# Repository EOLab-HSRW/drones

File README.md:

# EOLab's Drones System

EOLab's Drone System aims to provide a framework that serves as an umbrella to operate all our self-built drones. In this documentation you will find all the necessary resources for: specifications of our drones, 3D models for reference, operation manuals and general conventions used in all our platforms.

> [!IMPORTANT]
> If you are new, the best way to start is reading the ➡️ [Introduction](/introduction/) ⬅️ for these docs.

> The [EOLab](https://www.eolab.de/) (Earth Observation Lab) is a laboratory of the [Rhine-Waal University of Applied Sciences (HSRW)](https://www.hochschule-rhein-waal.de/de) in Germany. It is part of the [Faculty of Communication and Environment](https://www.hochschule-rhein-waal.de/de/fakultaeten/kommunikation-und-umwelt), Campus Kamp-Lintfort.

## Drones

| Drone Name                                                                                                                                       | Self-built | Quantity | Status               |
|--------------------------------------------------------------------------------------------------------------------------------------------------|:----------:|:--------:|----------------------|
| [SAR](./sar/)                                                                                                                                    | ✅         | 1        | 🟡 Under test        |
| [Platypus](./platypus/)                                                                                                                          | ✅         | 1        | 🟡 Under test        |
| [Protoflyer](./protoflyer/)                                                                                                                      | ✅         | ?        | 🟡 Under test        |
| [Phoenix](./phoenix/)                                                                                                                            | ✅         | 1        | 🟡 Under test        |
| [Condor](./condor/)                                                                                                                              | ✅         | 1        | 🟡 Under test        |
| [Pegasus](./pegasus/)                                                                                                                            | ✅         | 1        | 🟡 Under test        |
| Octopus                                                                                                                                          | ✅         | 1        | 🟡 Under maintenance |
| Mantis                                                                                                                                           | ✅         | 1        | 🟡 Under maintenance |
| Cargo Drone                                                                                                                                      | ✅         | 1        | 🟡 Under maintenance |
| DJI Tello EDU <br> - [User Manual](https://dl-cdn.ryzerobotics.com/downloads/Tello/Tello%20User%20Manual%20v1.4.pdf)                             |            | 2?       | 🟢 Operational       |
| DJI RoboMaster TT Tello Talent <br> - [User Manual](https://dl.djicdn.com/downloads/RoboMaster+TT/RoboMaster_TT_Tello_Talent_User_Manual_en.pdf) |            | ?        | 🟢 Operational       |
| DJI Phantom 4 Pro <br> - [User Manual](https://dl.djicdn.com/downloads/phantom_4_pro/Phantom+4+Pro+Pro+Plus+User+Manual+v1.0.pdf)                |            | 1        | 🟢 Operational       |
| DJI NEO <br> - [User Manual](https://dl.djicdn.com/downloads/neo/20240905/DJI_Neo_User_Manual_v1.0_en.pdf)                                       |            | 1        | 🟢 Operational       |
| DJI Mini 4 Pro <br> - [User Manual](https://dl.djicdn.com/downloads/DJI_Mini_4_Pro/DJI_Mini_4_Pro_User_Manual_EN.pdf)                            |            | 1        | 🟢 Operational       |
| DJI Avata <br> - [User Manual](https://www.foto.no/media/multicase/documents/dji/dji%20avata%20user%20manual%20v1.06.pdf)                        |            | 1        | 🟢 Operational       |
| DJI Mavic 3M <br> - [User Manual](https://dl.djicdn.com/downloads/DJI_Mavic_3_Enterprise/20221216/DJI_Mavic_3M_User_Manual-EN.pdf)               |            | 1        | 🟢 Operational       |
| AR Drone 2.0                                                                                                                                     |            | 2        | 🟢 Operational       |

## Components

In our system, a "component" can be any extra device like a RC Controller or a payload that interact with the our drones. Our system components are designed to be combinable, so that they can be interchanged with any of our self-built drones, all the necessary parameters to integrate the component(s) into the drone are added in the drone firmware.

| Component                                                                                                                                                                                                                           | Quantity | Compatibility      |
|-------------------------------------------------------------------------------------------------------------------------------------------------------------------------------------------------------------------------------------|:--------:|--------------------|
| [Radiomaster TX16s (with ELRS radio module)](https://www.radiomasterrc.com/products/tx16s-mark-ii-radio-controller?variant=45864311685351)<br> - [User Manual](https://cdn.shopify.com/s/files/1/0609/8324/7079/files/TX16S_1.pdf)  | 1        | only `self-builts` |
| [RP1 V2 Receiver (with external antenna)](https://www.radiomasterrc.com/products/rp1-expresslrs-2-4ghz-nano-receiver) <br> - [User Manual](https://cdn.shopify.com/s/files/1/0609/8324/7079/files/RP1_User_Manual.pdf?v=1722923320) | 2?       | only `self-builts`  |
| [RP2 V2 Receiver (with ceramic antenna)](https://www.radiomasterrc.com/products/rp2-expresslrs-2-4ghz-nano-receiver) <br> - [User Manual](https://cdn.shopify.com/s/files/1/0609/8324/7079/files/RP2_User_Manual.pdf?v=1722923303)  | 2?       | only `self-builts`  |
| [EMLID Reach RS3](https://emlid.com/reachrs3/)<br> - [User Manual](https://docs.emlid.com/reachrs3/) | 2 | for DJI drones |
| [EMLID Reach RS2+](https://emlid.com/reachrs2plus/)<br> - [User Manual](https://docs.emlid.com/reachrs2/) | 2 | for DJI drones |

## Misc Utils

| Type    | Misc Utils                                                                                                                                                                                                                                                                                                                                                                                                                          | Quantity |
|---------|-------------------------------------------------------------------------------------------------------------------------------------------------------------------------------------------------------------------------------------------------------------------------------------------------------------------------------------------------------------------------------------------------------------------------------------|----------|
| Charger | Graupner Ultramat 18 (Graupner went bankrupt in 2012)<br> - [User Manual](https://www.manualslib.de/manual/51049/Graupner-Ultramat-18.html)                                                                                                                                                                                                                                                                                         | 1        |
| Charger | [Voltcraft V-Charge 200 DUO](https://www.conrad.de/de/p/voltcraft-v-charge-200-duo-modellbau-multifunktionsladegeraet-12-v-230-v-10-a-blei-nimh-nicd-lipo-liion-lihv-blei-1539603.html)<br> - [User Manual](https://asset.conrad.com/media10/add/160267/c1/-/en/001539603ML02/upute-za-rukovanje-1539603-voltcraft-v-charge-200-duo-visenamjenski-punjac-baterija-za-modele-12-v-230-v-10-a-olovni-nikalj-metal-hidridni-nikal.pdf) | 1        |
| Charger | iMax B6AC <br> - [User Manual](https://www.pololu.com/file/0j525/imaxb6acmanual.pdf)                                                                                                                                                                                                                                                                                                                                                | 1        |
| Charger | [Tattu TA3000 Dual Smart Charger](https://genstattu.com/tattu-dual-smart-charger-60a-3000w-for-6s-12s-14s-lipo-lihv-tattu-smart-battery/)<br> - [User Manual](https://genstattu.com/content/instock/TA3000.pdf?srsltid=AfmBOoqkx91cG-YnTiC2ZcBJFpmeLNBOX0O4IQl7vUg3wHW8a9Hnu5sL)                                                                                                                                                    | 1        |

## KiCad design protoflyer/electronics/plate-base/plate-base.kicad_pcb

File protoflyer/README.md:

# Protoflyer

## Components

| Component | Model                                     | Ref Link                                                             | Documentation                                                                                         |
|-----------|-------------------------------------------|----------------------------------------------------------------------|-------------------------------------------------------------------------------------------------------|
| FMU       | Hex Cube Black                            | [link](https://docs.px4.io/main/en/flight_controller/pixhawk-2.html) | [The Cube Module Overview](https://docs.cubepilot.org/user-guides/autopilot/the-cube-module-overview) |
| Motor     | DJI 2312E Motor (as part of the DJI E305) | (obsolete)                                                           | [DJI E305 Propulsion System](https://dl.djicdn.com/downloads/e305/en/E305_User_Manual_v1.00_en.pdf)   |
| ESC       | DJI 420LITE ESC (as part of the DJI E305) | (obsolete)                                                           | [DJI E305 Propulsion System](https://dl.djicdn.com/downloads/e305/en/E305_User_Manual_v1.00_en.pdf)   |
| Propeller | DJI 9450 (as part of the DJI E305)        | (obsolete)                                                           | [DJI E305 Propulsion System](https://dl.djicdn.com/downloads/e305/en/E305_User_Manual_v1.00_en.pdf)   |

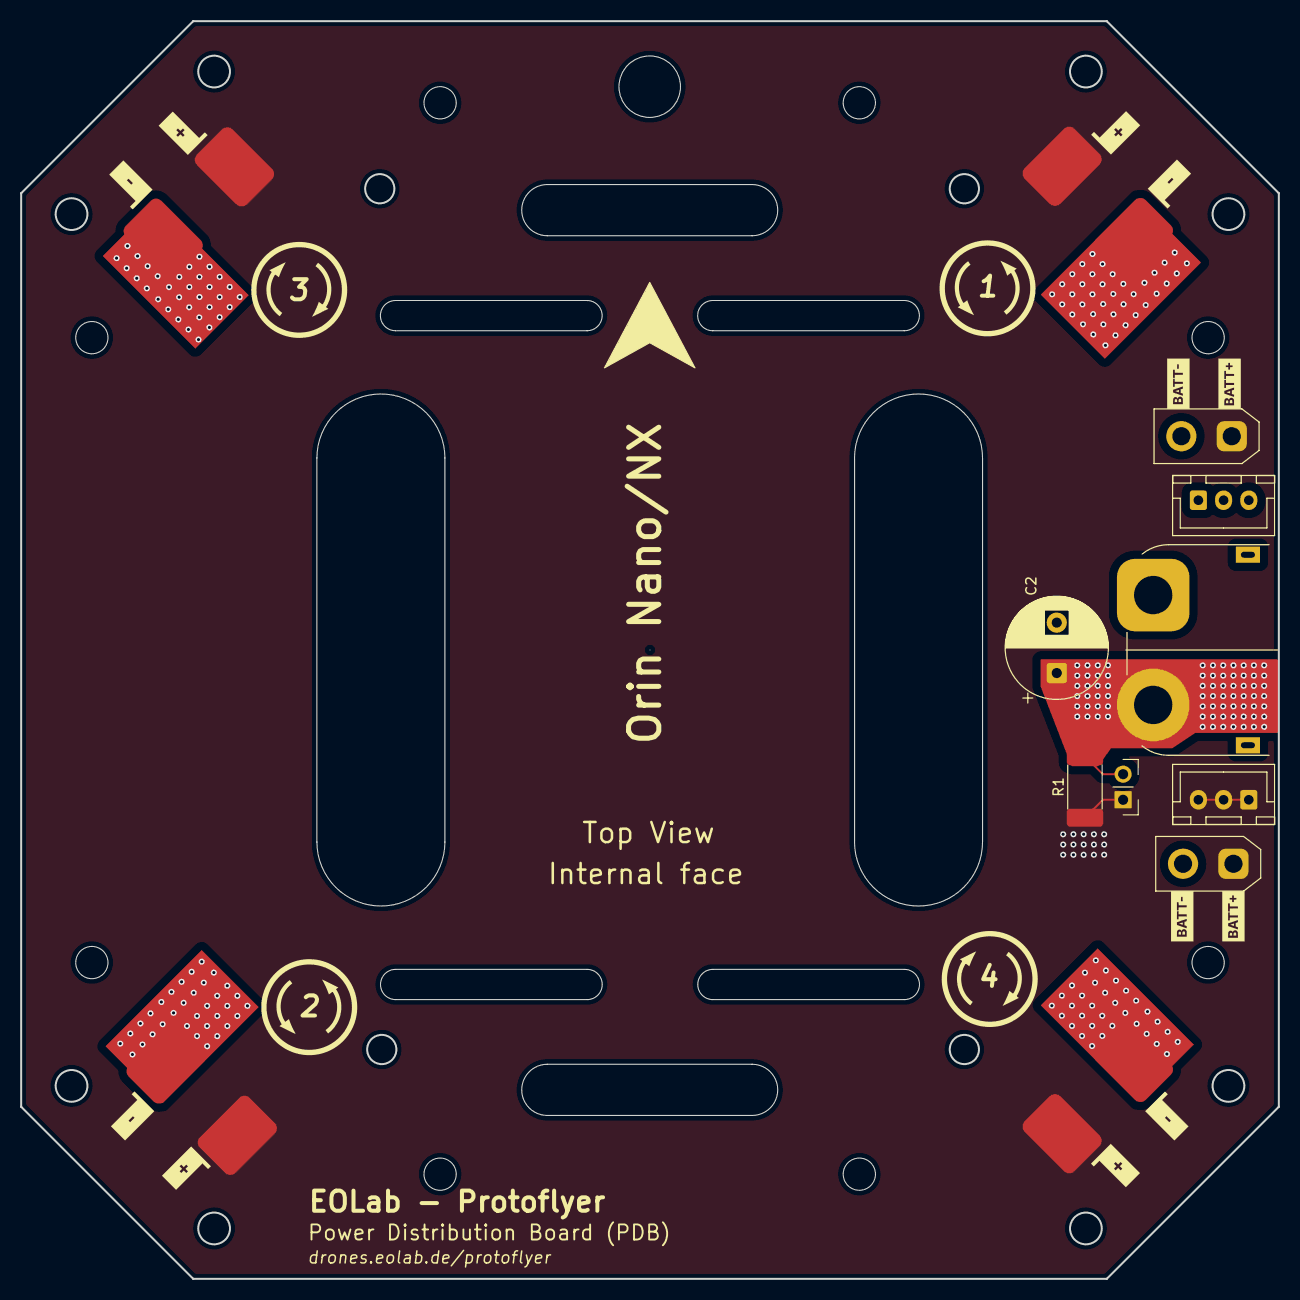
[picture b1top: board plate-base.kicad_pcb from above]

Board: 2 copper layers, 124.8 x 124.8 mm, 12 parts (0 on the bottom side), 3 nets.

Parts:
C2: 470u, 50V, 20%; CP_Radial_D10.0mm_P5.00mm
J1: Conn_01x02_Socket; AMASS_XT90PW-M_1x02_P10.90mm_Horizontal
J2, J3, J4, J5: Conn_01x02_Pin; Motor Solder Pad
J6, J11: Conn_01x03_Pin; JST_XH_B3B-XH-A_1x03_P2.50mm_Vertical
J8, J9: Conn_01x02_Pin; AMASS_XT30UPB-F_1x02_P5.0mm_Vertical
J10: Conn_01x02_Pin; PinHeader_1x02_P2.54mm_Vertical
R1: 500u, 1%, 10 W; R_2512_6332Metric_Pad1.40x3.35mm_HandSolder

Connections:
+BATT: C2.1, J1.2, J10.2, R1.4
-BATT: C2.2, J1.1, J2.2, J3.2, J4.2, J5.2, J6.1, J6.2, J6.3, J8.2, J9.2
VBUS: J2.1, J3.1, J4.1, J5.1, J8.1, J9.1, J10.1, J11.1, J11.2, J11.3, R1.1

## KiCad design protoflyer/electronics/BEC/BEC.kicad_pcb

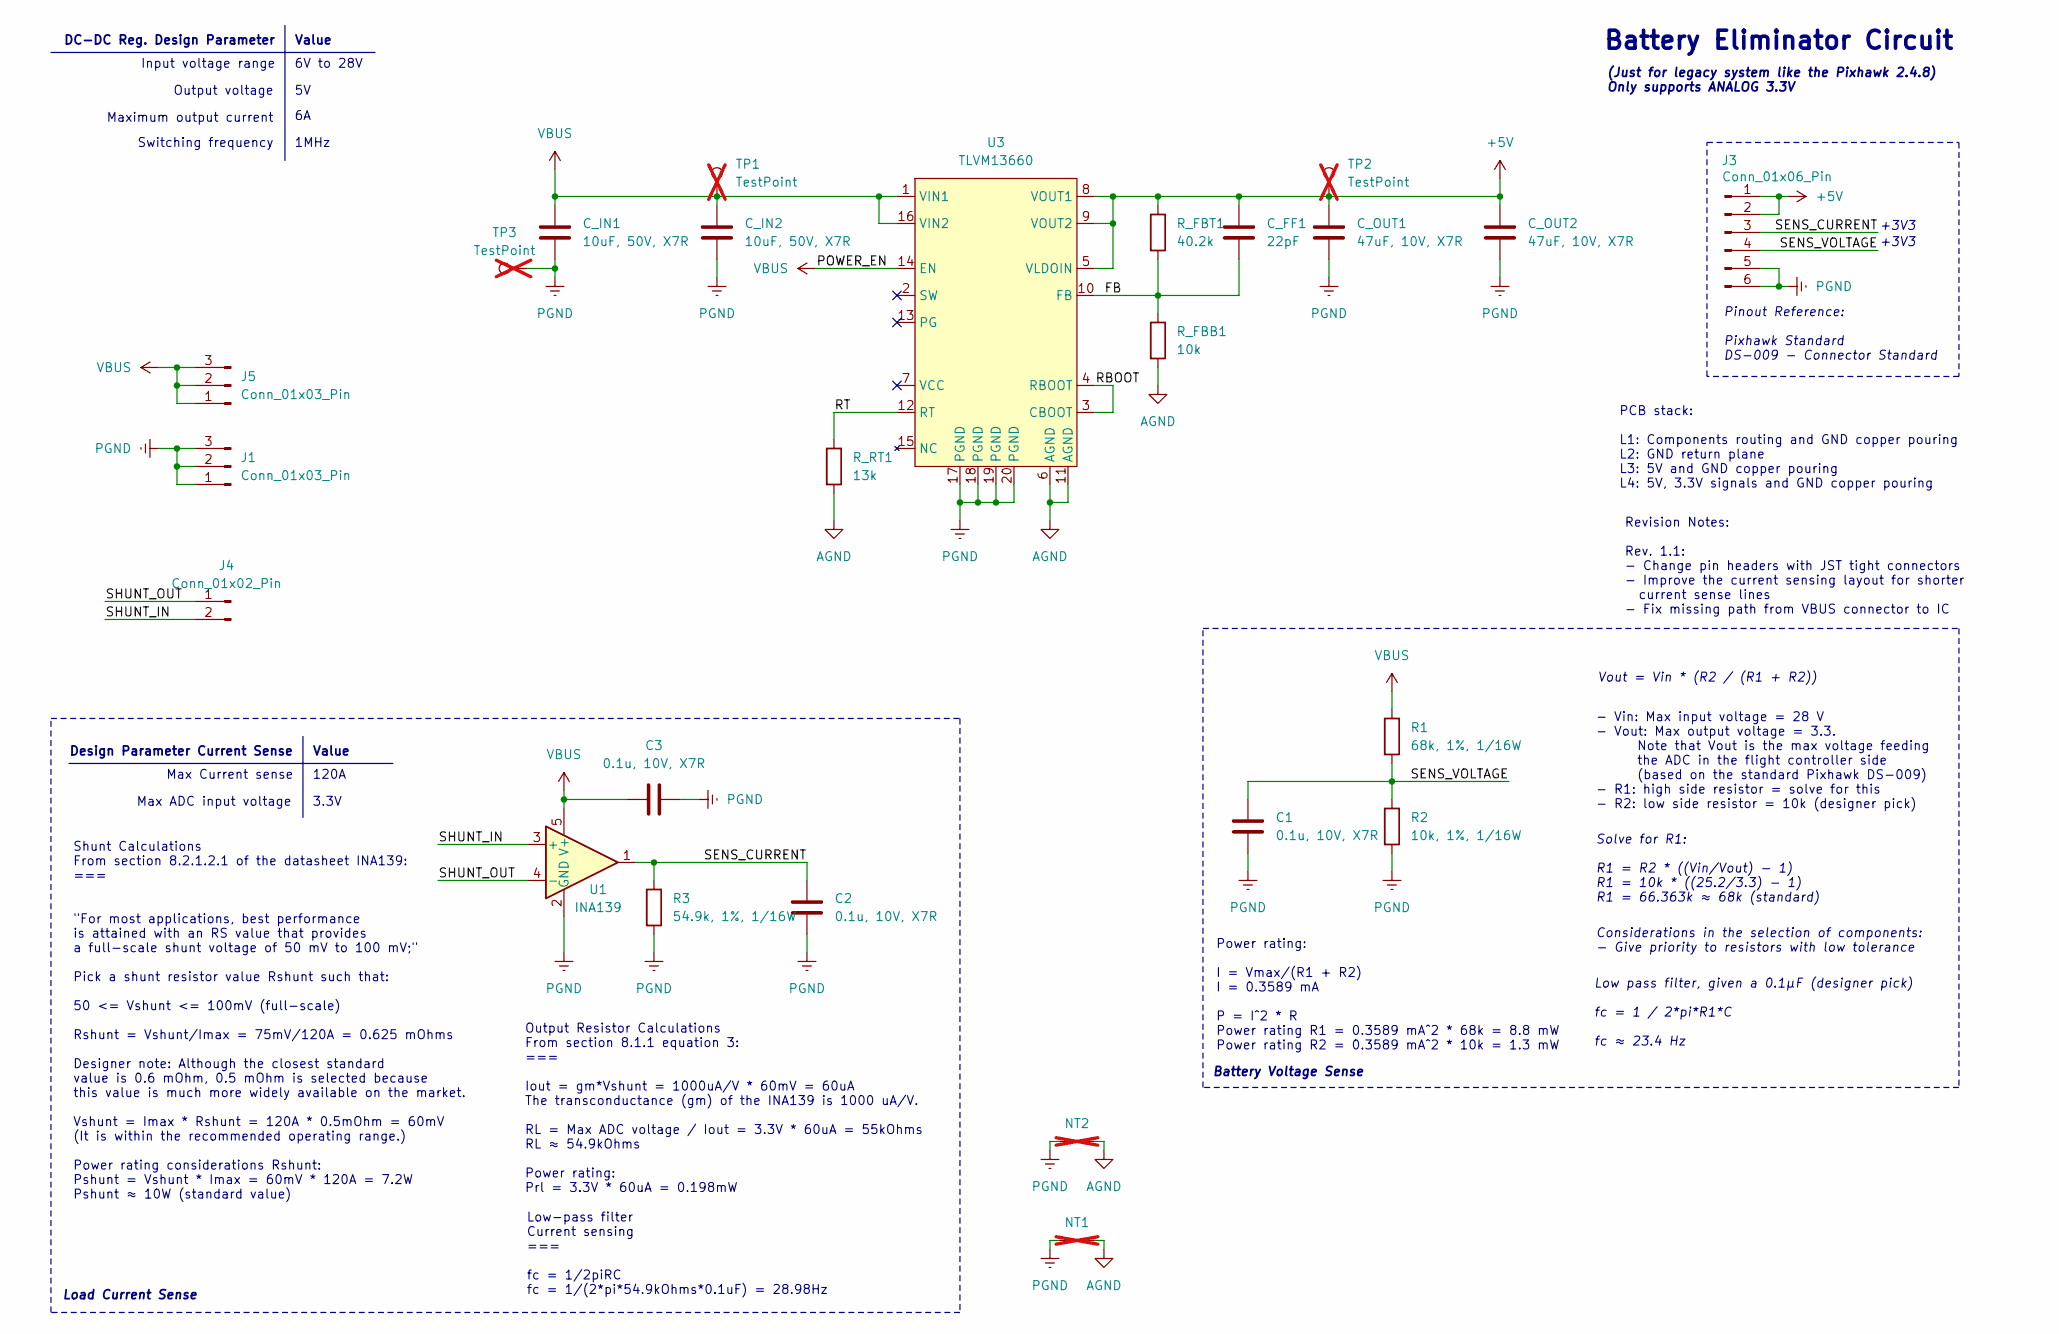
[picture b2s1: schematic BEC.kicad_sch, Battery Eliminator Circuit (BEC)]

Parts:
C1, C2, C3: 0.1u, 10V, X7R; C_0402_1005Metric_Pad0.74x0.62mm_HandSolder; Digikey No 587-3769-1-ND
C_FF1: 22pF; C_0402_1005Metric_Pad0.74x0.62mm_HandSolder; Digikey No 732-7427-1-ND
C_IN1, C_IN2: 10uF, 50V, X7R; C_1210_3225Metric_Pad1.33x2.70mm_HandSolder; Digikey No 587-3166-1-ND
C_OUT1, C_OUT2: 47uF, 10V, X7R; C_1210_3225Metric_Pad1.33x2.70mm_HandSolder; Digikey No 587-5921-1-ND
J1, J5: Conn_01x03_Pin; SHDR3W80P0X250_1X3_1000X600X950P; Digikey No 455-2966-ND
J3: Conn_01x06_Pin; JST_GH_SM06B-GHS-TB_1x06-1MP_P1.25mm_Horizontal; Digikey No 455-1568-2-ND
J4: Conn_01x02_Pin; PinHeader_1x02_P2.54mm_Vertical
NT1, NT2: NetTie_2; NetTie-2_SMD_Pad0.5mm; not fitted
R1: 68k, 1%, 1/16W; R_0402_1005Metric; Digikey No RMCF0402FT68K0CT-ND
R2: 10k, 1%, 1/16W; R_0402_1005Metric; Digikey No RMCF0402FT10K0CT-ND
R3: 54.9k, 1%, 1/16W; R_0402_1005Metric; Digikey No 13-RC0402FR-1354K9LCT-ND
R_FBB1: 10k; R_0603_1608Metric_Pad0.98x0.95mm_HandSolder; Digikey No 311-10.0KHRCT-ND
R_FBT1: 40.2k; R_0603_1608Metric_Pad0.98x0.95mm_HandSolder; Digikey No 311-40.2KHRCT-ND
R_RT1: 13k; R_0603_1608Metric_Pad0.98x0.95mm_HandSolder; Digikey No 311-13.0KHRCT-ND
TP1, TP2, TP3: TestPoint; TestPoint_Pad_D1.0mm; not fitted
U1: INA139; SOT-23-5; Digikey No INA139NA/250CT-ND
U3: TLVM13660; B3QFN20_RDL_TEX; Digikey No 296-TLVM13660RDLRCT-ND

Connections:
+5V: C_FF1.1, C_OUT1.1, C_OUT2.1, J3.1, J3.2, R_FBT1.1, TP2.1, U3.5 (VLDOIN), U3.8 (VOUT1), U3.9 (VOUT2)
/FB: C_FF1.2, R_FBB1.1, R_FBT1.2, U3.10 (FB)
/RBOOT: U3.3 (CBOOT), U3.4 (RBOOT)
/RT: R_RT1.1, U3.12 (RT)
/SENS_CURRENT: C2.1, J3.3, R3.1, U1.1
/SENS_VOLTAGE: C1.1, J3.4, R1.2, R2.1
/SHUNT_IN: J4.2, U1.3 (+)
/SHUNT_OUT: J4.1, U1.4 (-)
AGND: NT1.2, NT2.2, R_FBB1.2, R_RT1.2, U3.6 (AGND), U3.11 (AGND)
PGND: C1.2, C2.2, C3.2, C_IN1.2, C_IN2.2, C_OUT1.2, C_OUT2.2, J1.1, J1.2, J1.3, J3.5, J3.6, NT1.1, NT2.1, R2.2, R3.2, TP3.1, U1.2 (GND), U3.17 (PGND), U3.18 (PGND), U3.19 (PGND), U3.20 (PGND)
VBUS: C3.1, C_IN1.1, C_IN2.1, J5.1, J5.2, J5.3, R1.1, TP1.1, U1.5 (V+), U3.1 (VIN1), U3.14 (EN), U3.16 (VIN2)

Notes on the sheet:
Revision Notes: Rev. 1.1: - Change pin headers with JST tight connectors - Improve the current sensing layout for shorter current sense lines - Fix missing path from VBUS connector to IC
DC-DC Reg. Design Parameter
Load Current Sense
+3V3
Solve for R1: R1 = R2 * ((Vin/Vout) - 1) R1 = 10k * ((25.2/3.3) - 1) R1 = 66.363k ≈ 68k (standard)
Value
Pinout Reference: Pixhawk Standard DS-009 - Connector Standard
Maximum output current
Switching frequency
Battery Voltage Sense
PCB stack: L1: Components routing and GND copper pouring L2: GND return plane L3: 5V and GND copper pouring L4: 5V, 3.3V signals and GND copper pouring
Max Current sense
Vout = Vin * (R2 / (R1 + R2))
Design Parameter Current Sense
Shunt Calculations From section 8.2.1.2.1 of the datasheet INA139: === "For most applications, best performance is attained with an RS value that provides a full-scale shunt voltage of 50 mV to 100 mV;" Pick a shunt resistor value Rshunt such that: 50 <= Vshunt <= 100mV (full-scale) Rshunt = Vshunt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
Power rating: I = Vmax/(R1 + R2) I = 0.3589 mA P = I^2 * R Power rating R1 = 0.3589 mA^2 * 68k = 8.8 mW Power rating R2 = 0.3589 mA^2 * 10k = 1.3 mW
- Vin: Max input voltage = 28 V - Vout: Max output voltage = 3.3. Note that Vout is the max voltage feeding the ADC in the flight controller side (based on the standard Pixhawk DS-009) - R1: high side resistor = solve for this - R2: low side resistor = 10k (designer pick)
Output Resistor Calculations From section 8.1.1 equation 3: === Iout = gm*Vshunt = 1000uA/V * 60mV = 60uA The transconductance (gm) of the INA139 is 1000 uA/V. RL = Max ADC voltage / Iout = 3.3V * 60uA = 55kOhms RL ≈ 54.9kOhms Power rating: Prl = 3.3V * 60uA = 0.198mW
(Just for legacy system like the Pixhawk 2.4.8) Only supports ANALOG 3.3V
1MHz
120A
Battery Eliminator Circuit
Max ADC input voltage
Considerations in the selection of components: - Give priority to resistors with low tolerance
Low pass filter, given a 0.1μF (designer pick) fc = 1 / 2*pi*R1*C fc ≈ 23.4 Hz
Input voltage range
Low-pass filter Current sensing === fc = 1/2piRC fc = 1/(2*pi*54.9kOhms*0.1uF) = 28.98Hz
6V to 28V
Output voltage
3.3V

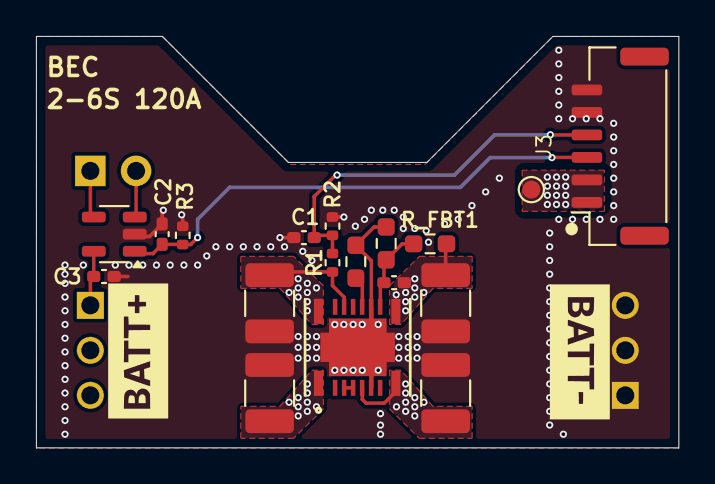
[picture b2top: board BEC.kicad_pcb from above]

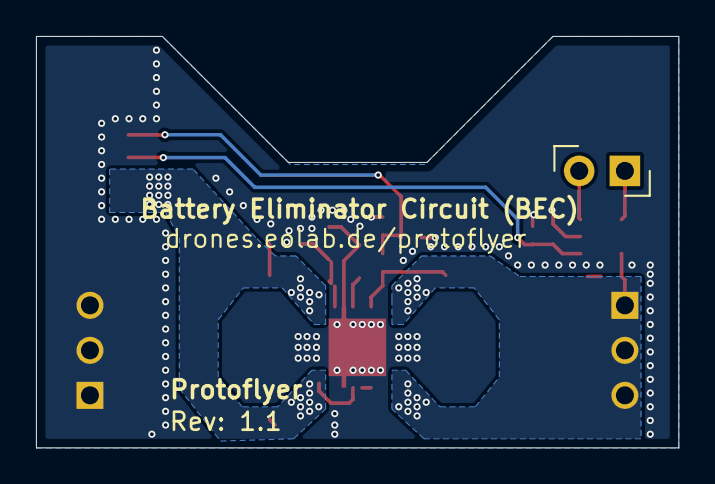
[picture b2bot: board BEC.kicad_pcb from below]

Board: 4 copper layers, 35.7 x 22.9 mm, 23 parts (2 on the bottom side), 11 nets.

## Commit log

2024-11-03 init repo
2024-11-08 add platypus drone
2024-11-09 add platypus firmware docs
2024-11-09 add transmitter docs
2024-11-09 update motor information
2024-11-18 update information
2024-11-20 add protoflyer
2024-11-21 add sar
2024-12-08 add extra info
2024-12-08 init docs
2024-12-08 fix docs path
2024-12-08 add base link to fix styling
2025-01-09 init phoenix docs
2025-01-09 add phoenix to table
2025-01-09 fix links
2025-01-09 add Wheelbase
2025-01-15 add DJI NEO
2025-01-15 add quantity
2025-01-15 add neo to sidebar
2025-01-16 add emergency switch
2025-01-16 update phoenix docs
2025-01-16 add flight mode table
2025-01-17 update docs
2025-01-22 update dev docs
2025-01-22 add mandatory files
2025-01-23 update components
2025-01-23 add mavic 3M
2025-01-24 fix typo and add emlid
2025-01-24 add user manual for EMLID
2025-01-25 add mission-protocol document
2025-02-10 add misc table
2025-02-10 move firmware tutorial to manual
2025-02-10 update sidebar
2025-02-10 fix pictures path
2025-02-10 move transmitter settings
2025-02-10 add toc to manual
2025-02-12 add Tattu charger
2025-02-12 add rangefinder
2025-02-13 fix link to file
2025-02-13 add condor
2025-02-13 add condor folder
2025-02-13 add info for condor
2025-02-13 add batteries
2025-02-14 re-arrange docs
2025-02-14 update modes
2025-02-14 fix broken link
2025-02-14 add operational-setup
2025-02-14 add entry
2025-02-14 fix title
2025-02-15 add rc mapping
2025-02-15 add note on FMU placement
2025-02-15 remove heading
2025-02-25 update radio information
2025-02-25 add section FMU radio settings
2025-02-25 add href to radio setup page
2025-02-25 update arm information
2025-03-03 update info sar
2025-03-04 add parm orientatiodiscuragen
2025-03-06 add eolab logo
2025-03-06 update info
2025-03-06 update estatus
2025-03-06 change key
2025-03-06 change link to internal link
2025-03-06 move esc calibration section
2025-03-09 add favicon
2025-03-09 update head
2025-03-09 add to public
2025-03-27 add flight zone
2025-03-27 add comp to platypus
2025-03-27 init batt docs
2025-03-28 update dry-weight
2025-04-07 add intro text
2025-04-07 update docs on battery charging
2025-04-08 refactor docs
2025-04-08 fix dead link
2025-04-08 fix typo on label
2025-04-08 update firmware
2025-04-08 re-arrange sidebar
2025-04-14 add link to RX
2025-04-28 update tables and add diagrams
2025-04-28 add condor to sidebar
2025-04-28 add dry weight
2025-05-08 add components to the list
2025-05-08 add extra information
2025-05-10 add acknowledgment
2025-05-10 thrust
2025-05-16 update flight modes
2025-05-27 update condor
2025-05-27 update table spec
2025-05-27 add flight tine
2025-05-27 clean format
2025-05-27 add ackonowledgment
2025-05-27 add linebreak
2025-05-27 update payload
2025-05-27 add dim tabldimenstione
2025-05-27 add dim file
2025-05-27 add condor dimentions
2025-06-13 add intall and init dev docs
2025-06-13 update maintainers
2025-06-13 add takeoff-and-land-demo
2025-06-13 update install
2025-06-13 add pip
2025-06-13 remove sudo from pip
2025-06-17 update commands
2025-06-20 update install steps
2025-06-20 add prerequisites
2025-06-23 add manual experimental
2025-07-21 add precision-landing-demo
2025-07-21 fix name
2025-07-25 change wording
2025-07-29 better ignore
2025-07-29 remap link for cleaner look but keeping the legacy style working
2025-08-15 update assigment
2025-08-19 init tools
2025-08-19 move to public
2025-08-19 fix ros ppa debian package
2025-08-19 change setup complete msg
2025-10-19 add detect-jetson script
2025-10-20 add script to handle NVIDIA gpu
2025-10-20 full script all-in-one nvidia checks
2025-10-20 add message
2025-10-20 add script to install opencv
2025-10-20 add handle for missing cuDNN
2025-10-21 add cleanup and improve cuda toolkit version install
2025-10-22 add note
2025-10-23 fix CUDA version mismatch a warning and not a faltal exit
2025-12-01 add link for UAV HOT guide
2025-12-07 add lacoro poster url
2025-12-09 remove image for now
2025-12-09 remove result image for now
2025-12-10 fix broken links
2025-12-19 add historical background
2025-12-19 Revert "add historical background"
    This reverts commit 7795c9da11dea8eac69a52072044da610c0a9040.
2025-12-19 add historical background with banner image
2025-12-19 update maintainers section
2025-12-19 fix link to introduction
2025-12-19 change order
2025-12-19 Revert "change order"
    This reverts commit 3918e04e7d283d8c6efc926d5846507645eccae6.
2025-12-19 Revert "Revert "change order""
    This reverts commit f554d59205eddb131d07c7fe634adb2bd370c29a.
2025-12-19 fix broken link to introduction
2026-01-12 add mesh note
2026-01-16 add Pegasus drone to catalog
2026-01-17 add info and diagrams for pegasus
2026-01-17 update maintainer notes
2026-01-19 add video on mission planning with QGroundControl
2026-01-21 protoflyer battery eliminator circuit (BEC) Rev. 1.1
    A more detail description of the changes can be found
    inside the schematic. Section "Revision Notes".
2026-01-22 protoflyer base-plate and power distribution board (PDB) Rev. 1.1
    A more detail description of the changes can be found
    inside the schematic. Section "Revision Notes".
2026-01-22 add explicit part number for AMASS connectors.
2026-01-25 remove unused table
2026-01-25 sync diagrams
2026-01-25 fix deadlink
2026-02-05 add new repo and status badges
2026-02-06 update list of repos
2026-02-09 add range
2026-02-09 fix typos
2026-04-29 fix spacing
2026-06-28 add new eolab_drone pypi publishing status
2026-06-28 add rosdep repo
